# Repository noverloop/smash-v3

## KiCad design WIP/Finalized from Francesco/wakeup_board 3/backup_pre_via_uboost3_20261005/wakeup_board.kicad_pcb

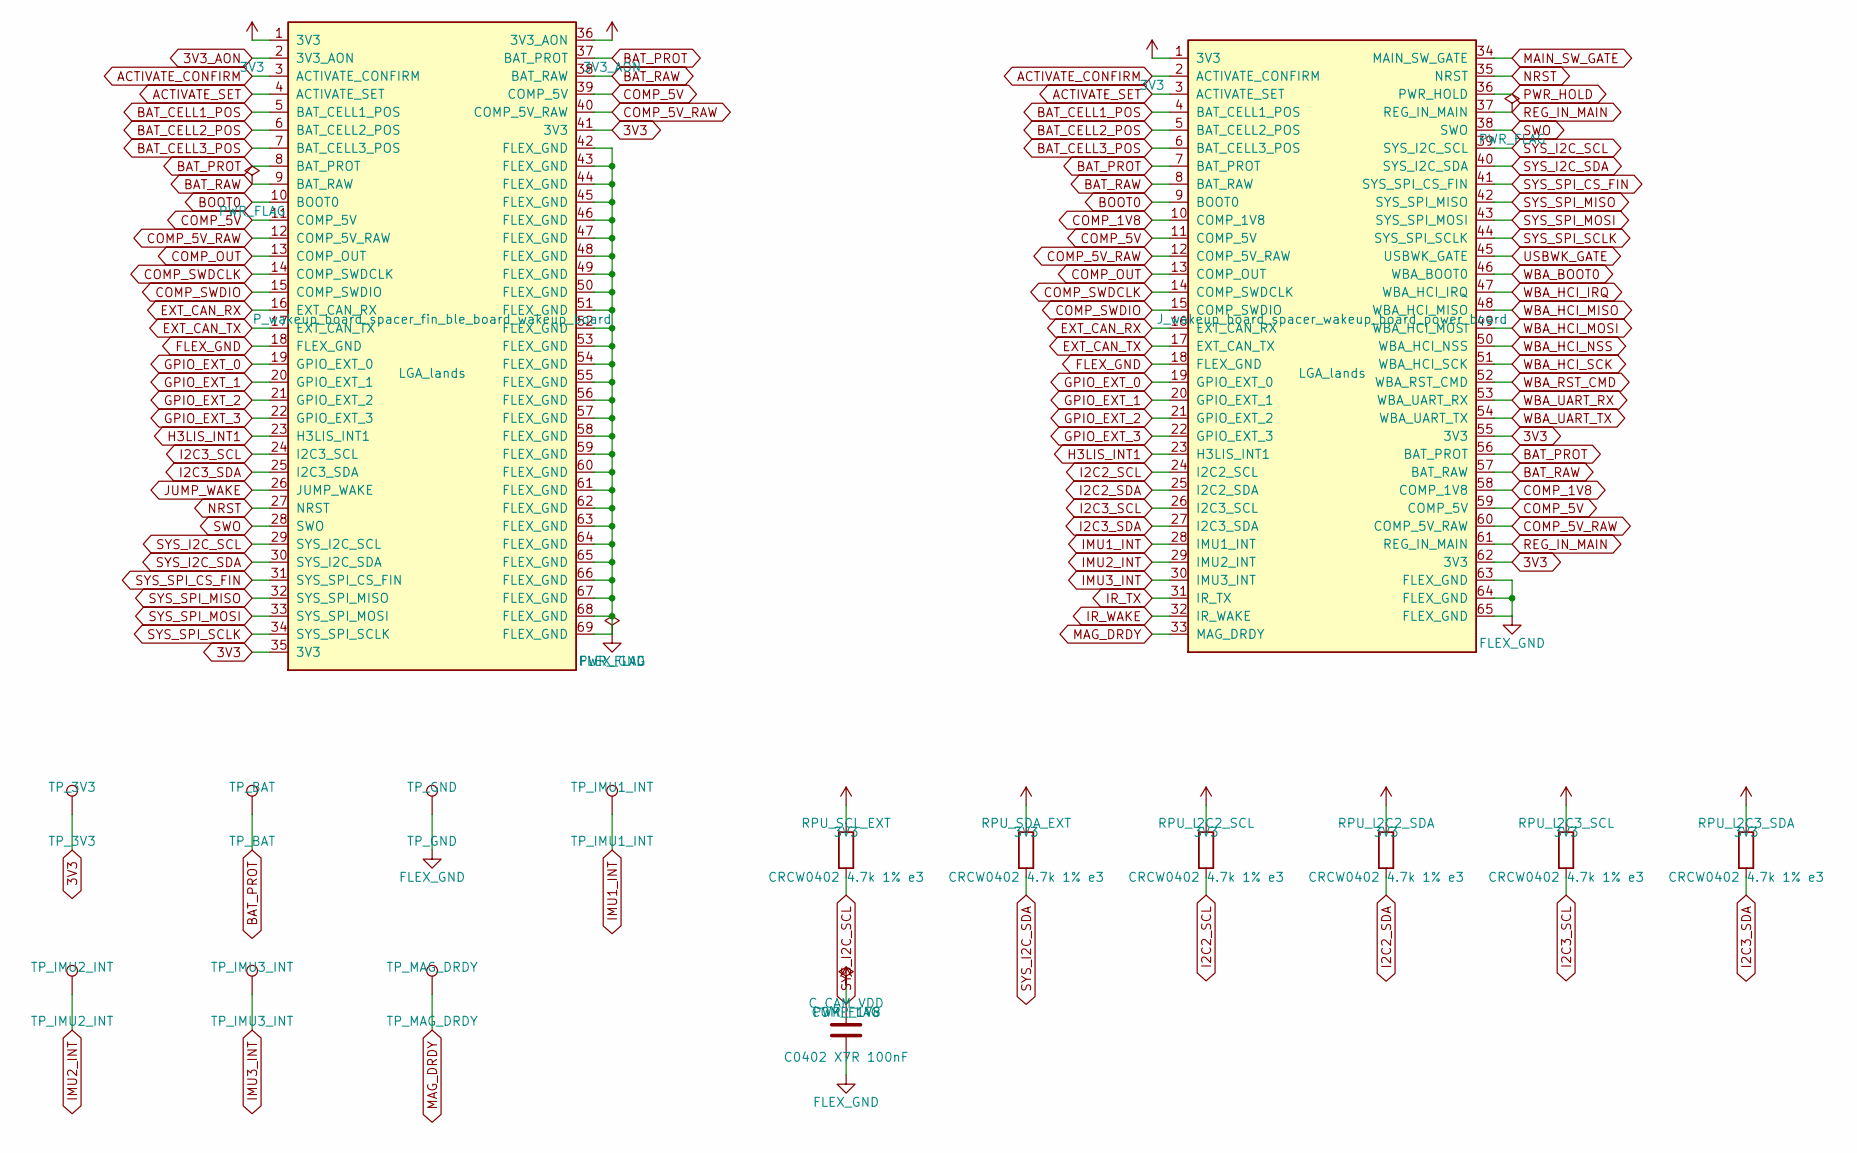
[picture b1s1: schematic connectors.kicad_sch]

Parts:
C_CAM_VDD: C0402 X7R 100nF; Capacitor_SMD_C_0402_1005Metric
J_wakeup_board_spacer_wakeup_board_power_board: LGA_lands; J_wakeup_board_spacer_wakeup_board_power_board
P_wakeup_board_spacer_fin_ble_board_wakeup_board: LGA_lands; P_wakeup_board_spacer_fin_ble_board_wakeup_board
RPU_I2C2_SCL, RPU_I2C2_SDA, RPU_I2C3_SCL, RPU_I2C3_SDA: CRCW0402 4.7k 1% e3; Resistor_SMD_R_0402_1005Metric
RPU_SCL_EXT: CRCW0402 4.7k 1% e3; Resistor_SMD_R_0402_1005Metric
RPU_SDA_EXT: CRCW0402 4.7k 1% e3; Resistor_SMD_R_0402_1005Metric
TP_3V3: TP_3V3; TestPoint_TestPoint_Pad_D1.5mm
TP_BAT: TP_BAT; TestPoint_TestPoint_Pad_D1.5mm
TP_GND: TP_GND; TestPoint_TestPoint_Pad_D1.5mm
TP_IMU1_INT: TP_IMU1_INT; TestPoint_TestPoint_Pad_D1.5mm
TP_IMU2_INT: TP_IMU2_INT; TestPoint_TestPoint_Pad_D1.5mm
TP_IMU3_INT: TP_IMU3_INT; TestPoint_TestPoint_Pad_D1.5mm
TP_MAG_DRDY: TP_MAG_DRDY; TestPoint_TestPoint_Pad_D1.5mm

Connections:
3V3: J_wakeup_board_spacer_wakeup_board_powe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.1 (3V3), J_wakeup_board_spacer_wakeup_board_powe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.55 (3V3), J_wakeup_board_spacer_wakeup_board_powe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.62 (3V3), P_wakeup_board_spacer_fin_ble_board_wak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.1 (3V3), P_wakeup_board_spacer_fin_ble_board_wak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.35 (3V3), P_wakeup_board_spacer_fin_ble_board_wak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.41 (3V3), RPU_I2C2_SCL.1, RPU_I2C2_SDA.1, RPU_I2C3_SCL.1, RPU_I2C3_SDA.1, RPU_SCL_EXT.1, RPU_SDA_EXT.1, TP_3V3.1; also elsewhere on the board
3V3_AON: P_wakeup_board_spacer_fin_ble_board_wak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.2 (3V3_AON), P_wakeup_board_spacer_fin_ble_board_wak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.36 (3V3_AON); also elsewhere on the board
ACTIVATE_CONFIRM: J_wakeup_board_spacer_wakeup_board_powe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.2 (ACTIVATE_CONFIRM), P_wakeup_board_spacer_fin_ble_board_wak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.3 (ACTIVATE_CONFIRM)
ACTIVATE_SET: J_wakeup_board_spacer_wakeup_board_powe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.3 (ACTIVATE_SET), P_wakeup_board_spacer_fin_ble_board_wak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.4 (ACTIVATE_SET)
BAT_CELL1_POS: J_wakeup_board_spacer_wakeup_board_powe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.4 (BAT_CELL1_POS), P_wakeup_board_spacer_fin_ble_board_wak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.5 (BAT_CELL1_POS)
BAT_CELL2_POS: J_wakeup_board_spacer_wakeup_board_powe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.5 (BAT_CELL2_POS), P_wakeup_board_spacer_fin_ble_board_wak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.6 (BAT_CELL2_POS)
BAT_CELL3_POS: J_wakeup_board_spacer_wakeup_board_powe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.6 (BAT_CELL3_POS), P_wakeup_board_spacer_fin_ble_board_wak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.7 (BAT_CELL3_POS)
BAT_PROT: J_wakeup_board_spacer_wakeup_board_powe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.7 (BAT_PROT), J_wakeup_board_spacer_wakeup_board_powe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.56 (BAT_PROT), P_wakeup_board_spacer_fin_ble_board_wak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.8 (BAT_PROT), P_wakeup_board_spacer_fin_ble_board_wak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.37 (BAT_PROT), TP_BAT.1; also elsewhere on the board
BAT_RAW: J_wakeup_board_spacer_wakeup_board_powe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.8 (BAT_RAW), J_wakeup_board_spacer_wakeup_board_powe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.57 (BAT_RAW), P_wakeup_board_spacer_fin_ble_board_wak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.9 (BAT_RAW), P_wakeup_board_spacer_fin_ble_board_wak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.38 (BAT_RAW); also elsewhere on the board
BOOT0: J_wakeup_board_spacer_wakeup_board_powe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.9 (BOOT0), P_wakeup_board_spacer_fin_ble_board_wak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.10 (BOOT0)
COMP_1V8: C_CAM_VDD.1, J_wakeup_board_spacer_wakeup_board_powe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.10 (COMP_1V8), J_wakeup_board_spacer_wakeup_board_powe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.58 (COMP_1V8)
COMP_5V: J_wakeup_board_spacer_wakeup_board_powe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.11 (COMP_5V), J_wakeup_board_spacer_wakeup_board_powe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.59 (COMP_5V), P_wakeup_board_spacer_fin_ble_board_wak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.11 (COMP_5V), P_wakeup_board_spacer_fin_ble_board_wak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.39 (COMP_5V)
COMP_5V_RAW: J_wakeup_board_spacer_wakeup_board_powe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.12 (COMP_5V_RAW), J_wakeup_board_spacer_wakeup_board_powe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.60 (COMP_5V_RAW), P_wakeup_board_spacer_fin_ble_board_wak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.12 (COMP_5V_RAW), P_wakeup_board_spacer_fin_ble_board_wak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.40 (COMP_5V_RAW)
COMP_OUT: J_wakeup_board_spacer_wakeup_board_powe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.13 (COMP_OUT), P_wakeup_board_spacer_fin_ble_board_wak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.13 (COMP_OUT)
COMP_SWDCLK: J_wakeup_board_spacer_wakeup_board_powe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.14 (COMP_SWDCLK), P_wakeup_board_spacer_fin_ble_board_wak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.14 (COMP_SWDCLK)
COMP_SWDIO: J_wakeup_board_spacer_wakeup_board_powe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.15 (COMP_SWDIO), P_wakeup_board_spacer_fin_ble_board_wak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.15 (COMP_SWDIO)
EXT_CAN_RX: J_wakeup_board_spacer_wakeup_board_powe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.16 (EXT_CAN_RX), P_wakeup_board_spacer_fin_ble_board_wak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.16 (EXT_CAN_RX)
EXT_CAN_TX: J_wakeup_board_spacer_wakeup_board_powe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.17 (EXT_CAN_TX), P_wakeup_board_spacer_fin_ble_board_wak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.17 (EXT_CAN_TX)
FLEX_GND: C_CAM_VDD.2, J_wakeup_board_spacer_wakeup_board_powe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.18 (FLEX_GND), J_wakeup_board_spacer_wakeup_board_powe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.63 (FLEX_GND), J_wakeup_board_spacer_wakeup_board_powe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.64 (FLEX_GND), J_wakeup_board_spacer_wakeup_board_powe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.65 (FLEX_GND), P_wakeup_board_spacer_fin_ble_board_wak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.18 (FLEX_GND), P_wakeup_board_spacer_fin_ble_board_wak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.42 (FLEX_GND), P_wakeup_board_spacer_fin_ble_board_wak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.43 (FLEX_GND), P_wakeup_board_spacer_fin_ble_board_wak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.44 (FLEX_GND), P_wakeup_board_spacer_fin_ble_board_wak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.45 (FLEX_GND), P_wakeup_board_spacer_fin_ble_board_wak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.46 (FLEX_GND), P_wakeup_board_spacer_fin_ble_board_wak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.47 (FLEX_GND), P_wakeup_board_spacer_fin_ble_board_wak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.48 (FLEX_GND), P_wakeup_board_spacer_fin_ble_board_wak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.49 (FLEX_GND), P_wakeup_board_spacer_fin_ble_board_wak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.50 (FLEX_GND), P_wakeup_board_spacer_fin_ble_board_wak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.51 (FLEX_GND), P_wakeup_board_spacer_fin_ble_board_wak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.52 (FLEX_GND), P_wakeup_board_spacer_fin_ble_board_wak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.53 (FLEX_GND), P_wakeup_board_spacer_fin_ble_board_wak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.54 (FLEX_GND), P_wakeup_board_spacer_fin_ble_board_wak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.55 (FLEX_GND), P_wakeup_board_spacer_fin_ble_board_wak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.56 (FLEX_GND), P_wakeup_board_spacer_fin_ble_board_wak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.57 (FLEX_GND), P_wakeup_board_spacer_fin_ble_board_wak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.58 (FLEX_GND), P_wakeup_board_spacer_fin_ble_board_wak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.59 (FLEX_GND), P_wakeup_board_spacer_fin_ble_board_wak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.60 (FLEX_GND), P_wakeup_board_spacer_fin_ble_board_wak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.61 (FLEX_GND), P_wakeup_board_spacer_fin_ble_board_wak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.62 (FLEX_GND), P_wakeup_board_spacer_fin_ble_board_wak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.63 (FLEX_GND), P_wakeup_board_spacer_fin_ble_board_wak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.64 (FLEX_GND), P_wakeup_board_spacer_fin_ble_board_wak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.65 (FLEX_GND), P_wakeup_board_spacer_fin_ble_board_wak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.66 (FLEX_GND), P_wakeup_board_spacer_fin_ble_board_wak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.67 (FLEX_GND), P_wakeup_board_spacer_fin_ble_board_wak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.68 (FLEX_GND), P_wakeup_board_spacer_fin_ble_board_wak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.69 (FLEX_GND), TP_GND.1; also elsewhere on the board
GPIO_EXT_0: J_wakeup_board_spacer_wakeup_board_powe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.19 (GPIO_EXT_0), P_wakeup_board_spacer_fin_ble_board_wak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.19 (GPIO_EXT_0)
GPIO_EXT_1: J_wakeup_board_spacer_wakeup_board_powe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.20 (GPIO_EXT_1), P_wakeup_board_spacer_fin_ble_board_wak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.20 (GPIO_EXT_1)
GPIO_EXT_2: J_wakeup_board_spacer_wakeup_board_powe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.21 (GPIO_EXT_2), P_wakeup_board_spacer_fin_ble_board_wak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.21 (GPIO_EXT_2)
GPIO_EXT_3: J_wakeup_board_spacer_wakeup_board_powe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.22 (GPIO_EXT_3), P_wakeup_board_spacer_fin_ble_board_wak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.22 (GPIO_EXT_3)
H3LIS_INT1: J_wakeup_board_spacer_wakeup_board_powe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.23 (H3LIS_INT1), P_wakeup_board_spacer_fin_ble_board_wak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.23 (H3LIS_INT1)
I2C2_SCL: J_wakeup_board_spacer_wakeup_board_powe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.24 (I2C2_SCL), RPU_I2C2_SCL.2; also elsewhere on the board
I2C2_SDA: J_wakeup_board_spacer_wakeup_board_powe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.25 (I2C2_SDA), RPU_I2C2_SDA.2; also elsewhere on the board
I2C3_SCL: J_wakeup_board_spacer_wakeup_board_powe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.26 (I2C3_SCL), P_wakeup_board_spacer_fin_ble_board_wak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.24 (I2C3_SCL), RPU_I2C3_SCL.2; also elsewhere on the board
I2C3_SDA: J_wakeup_board_spacer_wakeup_board_powe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.27 (I2C3_SDA), P_wakeup_board_spacer_fin_ble_board_wak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.25 (I2C3_SDA), RPU_I2C3_SDA.2; also elsewhere on the board
IMU1_INT: J_wakeup_board_spacer_wakeup_board_powe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.28 (IMU1_INT), TP_IMU1_INT.1; also elsewhere on the board
IMU2_INT: J_wakeup_board_spacer_wakeup_board_powe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.29 (IMU2_INT), TP_IMU2_INT.1; also elsewhere on the board
IMU3_INT: J_wakeup_board_spacer_wakeup_board_powe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.30 (IMU3_INT), TP_IMU3_INT.1; also elsewhere on the board
IR_TX: J_wakeup_board_spacer_wakeup_board_powe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.31 (IR_TX); also elsewhere on the board
IR_WAKE: J_wakeup_board_spacer_wakeup_board_powe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.32 (IR_WAKE); also elsewhere on the board
MAG_DRDY: J_wakeup_board_spacer_wakeup_board_powe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.33 (MAG_DRDY), TP_MAG_DRDY.1; also elsewhere on the board
MAIN_SW_GATE: J_wakeup_board_spacer_wakeup_board_powe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.34 (MAIN_SW_GATE); also elsewhere on the board
NRST: J_wakeup_board_spacer_wakeup_board_powe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.35 (NRST), P_wakeup_board_spacer_fin_ble_board_wak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.27 (NRST)
PWR_HOLD: J_wakeup_board_spacer_wakeup_board_powe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.36 (PWR_HOLD); also elsewhere on the board
REG_IN_MAIN: J_wakeup_board_spacer_wakeup_board_powe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.37 (REG_IN_MAIN), J_wakeup_board_spacer_wakeup_board_powe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.61 (REG_IN_MAIN); also elsewhere on the board
SWO: J_wakeup_board_spacer_wakeup_board_powe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.38 (SWO), P_wakeup_board_spacer_fin_ble_board_wak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.28 (SWO)
SYS_I2C_SCL: J_wakeup_board_spacer_wakeup_board_powe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.39 (SYS_I2C_SCL), P_wakeup_board_spacer_fin_ble_board_wak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.29 (SYS_I2C_SCL), RPU_SCL_EXT.2
SYS_I2C_SDA: J_wakeup_board_spacer_wakeup_board_powe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.40 (SYS_I2C_SDA), P_wakeup_board_spacer_fin_ble_board_wak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.30 (SYS_I2C_SDA), RPU_SDA_EXT.2
SYS_SPI_CS_FIN: J_wakeup_board_spacer_wakeup_board_powe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.41 (SYS_SPI_CS_FIN), P_wakeup_board_spacer_fin_ble_board_wak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.31 (SYS_SPI_CS_FIN)
SYS_SPI_MISO: J_wakeup_board_spacer_wakeup_board_powe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.42 (SYS_SPI_MISO), P_wakeup_board_spacer_fin_ble_board_wak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.32 (SYS_SPI_MISO)
SYS_SPI_MOSI: J_wakeup_board_spacer_wakeup_board_powe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.43 (SYS_SPI_MOSI), P_wakeup_board_spacer_fin_ble_board_wak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.33 (SYS_SPI_MOSI)
SYS_SPI_SCLK: J_wakeup_board_spacer_wakeup_board_powe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.44 (SYS_SPI_SCLK), P_wakeup_board_spacer_fin_ble_board_wak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.34 (SYS_SPI_SCLK)
USBWK_GATE: J_wakeup_board_spacer_wakeup_board_powe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.45 (USBWK_GATE); also elsewhere on the board
WBA_BOOT0: J_wakeup_board_spacer_wakeup_board_powe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.46 (WBA_BOOT0); also elsewhere on the board
WBA_HCI_IRQ: J_wakeup_board_spacer_wakeup_board_powe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.47 (WBA_HCI_IRQ); also elsewhere on the board
WBA_HCI_MISO: J_wakeup_board_spacer_wakeup_board_powe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.48 (WBA_HCI_MISO); also elsewhere on the board
WBA_HCI_MOSI: J_wakeup_board_spacer_wakeup_board_powe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.49 (WBA_HCI_MOSI); also elsewhere on the board
WBA_HCI_NSS: J_wakeup_board_spacer_wakeup_board_powe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.50 (WBA_HCI_NSS); also elsewhere on the board
WBA_HCI_SCK: J_wakeup_board_spacer_wakeup_board_powe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.51 (WBA_HCI_SCK); also elsewhere on the board
WBA_RST_CMD: J_wakeup_board_spacer_wakeup_board_powe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.52 (WBA_RST_CMD); also elsewhere on the board
WBA_UART_RX: J_wakeup_board_spacer_wakeup_board_powe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.53 (WBA_UART_RX); also elsewhere on the board
WBA_UART_TX: J_wakeup_board_spacer_wakeup_board_powe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.54 (WBA_UART_TX); also elsewhere on the board

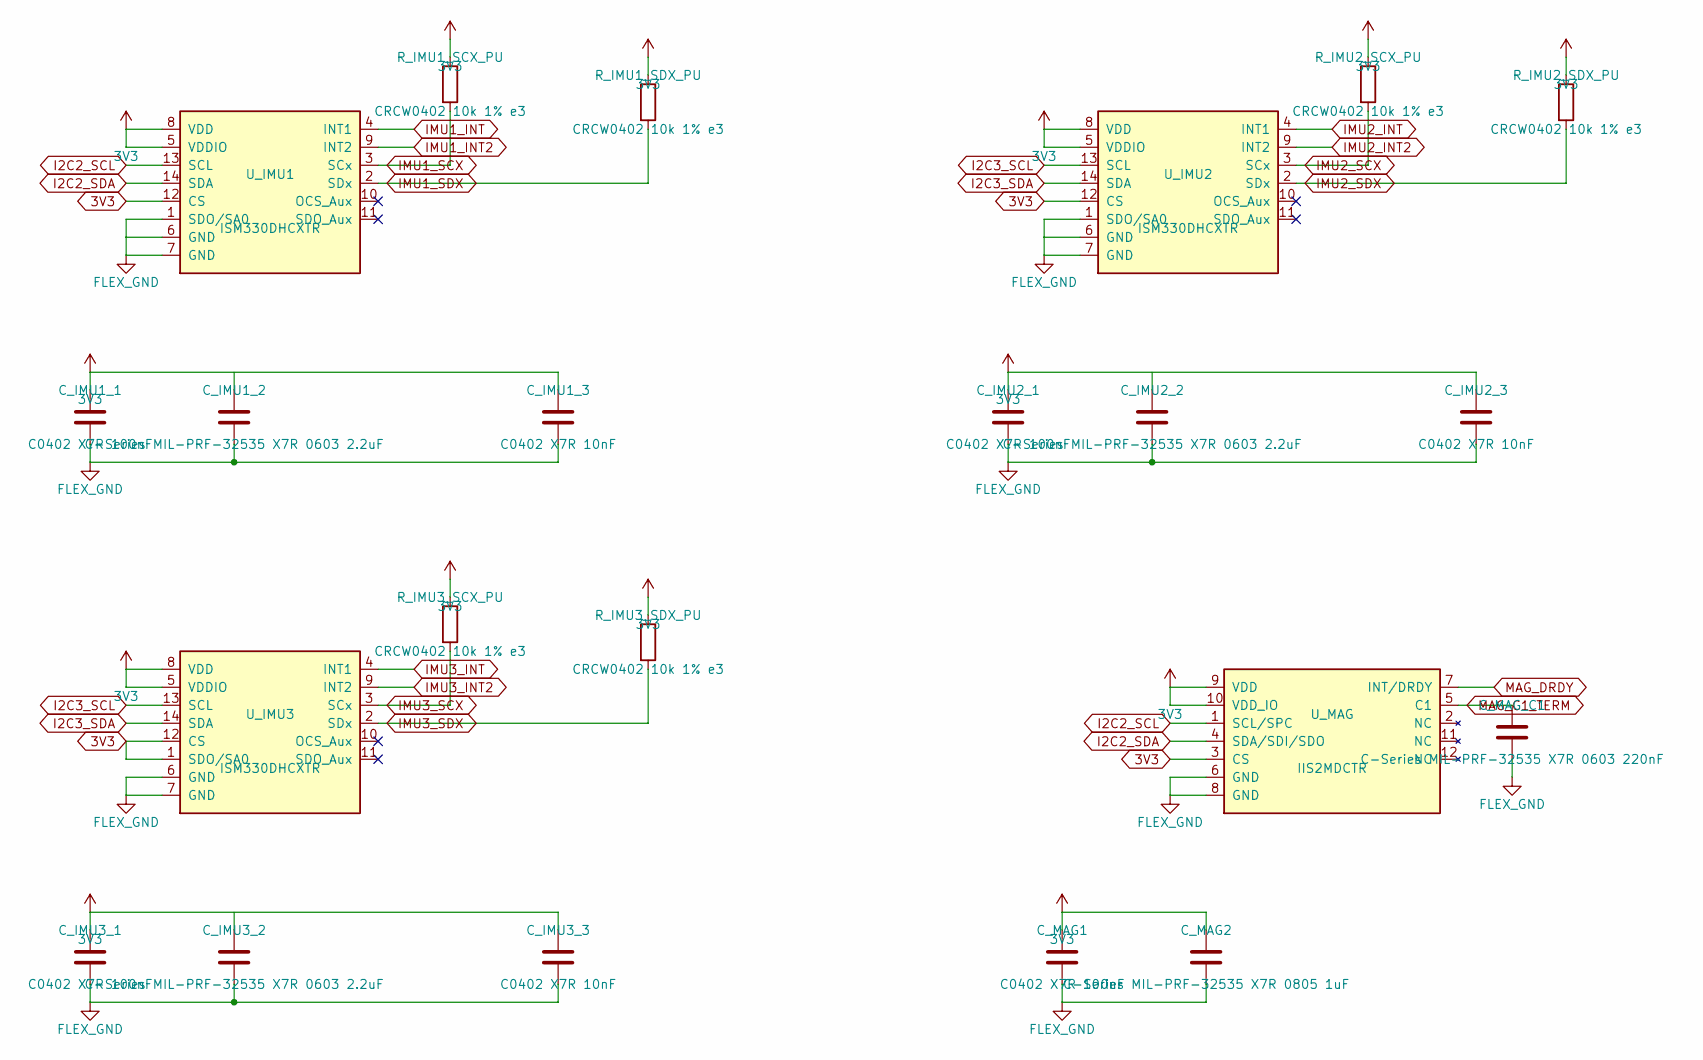
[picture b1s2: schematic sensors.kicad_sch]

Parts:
C_IMU1_1, C_IMU2_1, C_IMU3_1: C0402 X7R 100nF; Capacitor_SMD_C_0402_1005Metric
C_IMU1_2, C_IMU2_2, C_IMU3_2: C-Series MIL-PRF-32535 X7R 0603 2.2uF; Capacitor_SMD_C_0603_1608Metric
C_IMU1_3, C_IMU2_3, C_IMU3_3: C0402 X7R 10nF; Capacitor_SMD_C_0402_1005Metric
C_MAG1: C0402 X7R 100nF; Capacitor_SMD_C_0402_1005Metric
C_MAG2: C-Series MIL-PRF-32535 X7R 0805 1uF; Capacitor_SMD_C_0805_2012Metric
C_MAG_C1: C-Series MIL-PRF-32535 X7R 0603 220nF; Capacitor_SMD_C_0603_1608Metric
R_IMU1_SCX_PU, R_IMU1_SDX_PU, R_IMU2_SCX_PU, R_IMU2_SDX_PU, R_IMU3_SCX_PU, R_IMU3_SDX_PU: CRCW0402 10k 1% e3; Resistor_SMD_R_0402_1005Metric
U_IMU1, U_IMU2, U_IMU3: ISM330DHCXTR; LSM6DS3USTR (LGA-14)
U_MAG: IIS2MDCTR

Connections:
3V3: C_IMU1_1.1, C_IMU1_2.1, C_IMU1_3.1, C_IMU2_1.1, C_IMU2_2.1, C_IMU2_3.1, C_IMU3_1.1, C_IMU3_2.1, C_IMU3_3.1, C_MAG1.1, C_MAG2.1, R_IMU1_SCX_PU.1, R_IMU1_SDX_PU.1, R_IMU2_SCX_PU.1, R_IMU2_SDX_PU.1, R_IMU3_SCX_PU.1, R_IMU3_SDX_PU.1, U_IMU1.5 (VDDIO), U_IMU1.8 (VDD), U_IMU1.12 (CS), U_IMU2.5 (VDDIO), U_IMU2.8 (VDD), U_IMU2.12 (CS), U_IMU3.1 (SDO/SA0), U_IMU3.5 (VDDIO), U_IMU3.8 (VDD), U_IMU3.12 (CS), U_MAG.3 (CS), U_MAG.9 (VDD), U_MAG.10 (VDD_IO); also elsewhere on the board
FLEX_GND: C_IMU1_1.2, C_IMU1_2.2, C_IMU1_3.2, C_IMU2_1.2, C_IMU2_2.2, C_IMU2_3.2, C_IMU3_1.2, C_IMU3_2.2, C_IMU3_3.2, C_MAG1.2, C_MAG2.2, C_MAG_C1.2, U_IMU1.1 (SDO/SA0), U_IMU1.6 (GND), U_IMU1.7 (GND), U_IMU2.1 (SDO/SA0), U_IMU2.6 (GND), U_IMU2.7 (GND), U_IMU3.6 (GND), U_IMU3.7 (GND), U_MAG.6 (GND), U_MAG.8 (GND); also elsewhere on the board
I2C2_SCL: U_IMU1.13 (SCL), U_MAG.1 (SCL/SPC); also elsewhere on the board
I2C2_SDA: U_IMU1.14 (SDA), U_MAG.4 (SDA/SDI/SDO); also elsewhere on the board
I2C3_SCL: U_IMU2.13 (SCL), U_IMU3.13 (SCL); also elsewhere on the board
I2C3_SDA: U_IMU2.14 (SDA), U_IMU3.14 (SDA); also elsewhere on the board
IMU1_INT: U_IMU1.4 (INT1); also elsewhere on the board
IMU1_INT2: U_IMU1.9 (INT2)
IMU1_SCX: R_IMU1_SCX_PU.2, U_IMU1.3 (SCx)
IMU1_SDX: R_IMU1_SDX_PU.2, U_IMU1.2 (SDx)
IMU2_INT: U_IMU2.4 (INT1); also elsewhere on the board
IMU2_INT2: U_IMU2.9 (INT2)
IMU2_SCX: R_IMU2_SCX_PU.2, U_IMU2.3 (SCx)
IMU2_SDX: R_IMU2_SDX_PU.2, U_IMU2.2 (SDx)
IMU3_INT: U_IMU3.4 (INT1); also elsewhere on the board
IMU3_INT2: U_IMU3.9 (INT2)
IMU3_SCX: R_IMU3_SCX_PU.2, U_IMU3.3 (SCx)
IMU3_SDX: R_IMU3_SDX_PU.2, U_IMU3.2 (SDx)
MAG_C1_TERM: C_MAG_C1.1, U_MAG.5 (C1)
MAG_DRDY: U_MAG.7 (INT/DRDY); also elsewhere on the board

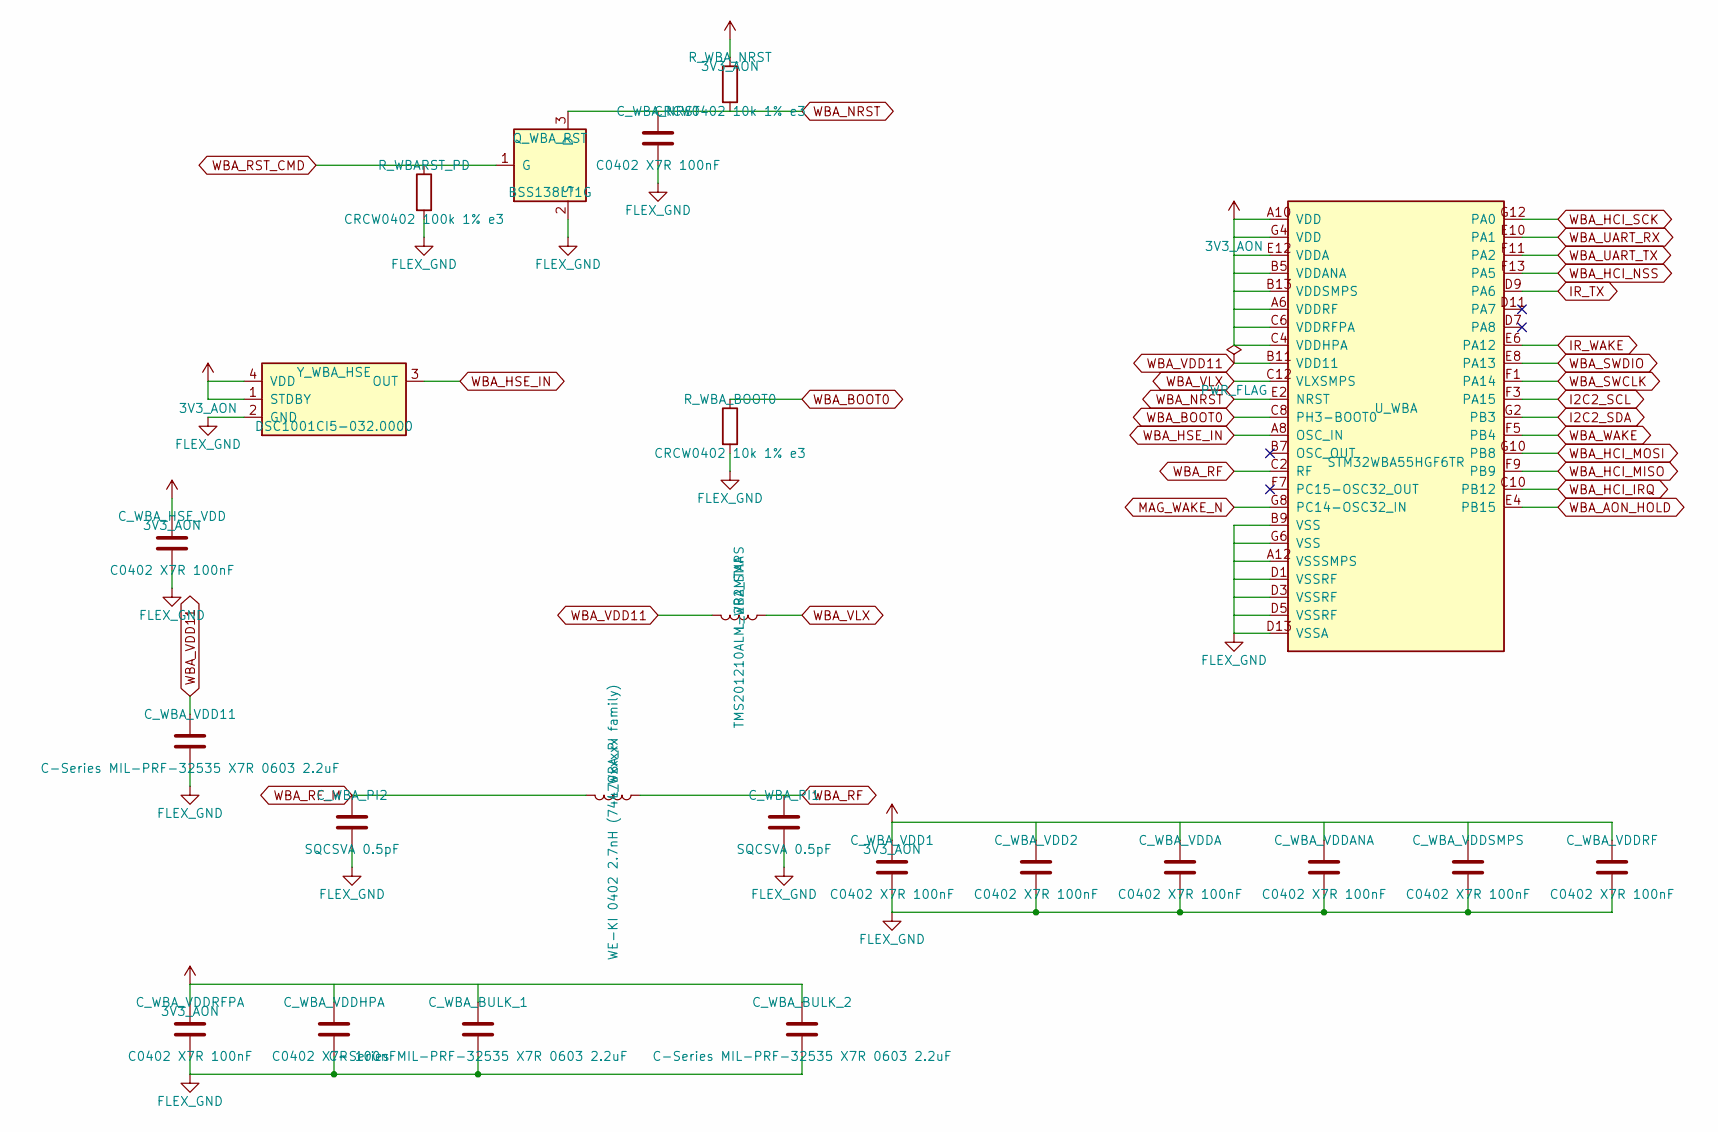
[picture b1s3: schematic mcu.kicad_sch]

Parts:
C_WBA_BULK_1, C_WBA_BULK_2: C-Series MIL-PRF-32535 X7R 0603 2.2uF; Capacitor_SMD_C_0603_1608Metric
C_WBA_HSE_VDD: C0402 X7R 100nF; Capacitor_SMD_C_0402_1005Metric
C_WBA_NRST: C0402 X7R 100nF; Capacitor_SMD_C_0402_1005Metric
C_WBA_PI1: SQCSVA 0.5pF; Capacitor_SMD_C_0402_1005Metric
C_WBA_PI2: SQCSVA 0.5pF; Capacitor_SMD_C_0603_1608Metric
C_WBA_VDD1, C_WBA_VDD2: C0402 X7R 100nF; Capacitor_SMD_C_0402_1005Metric
C_WBA_VDD11: C-Series MIL-PRF-32535 X7R 0603 2.2uF; Capacitor_SMD_C_0402_1005Metric
C_WBA_VDDA: C0402 X7R 100nF; Capacitor_SMD_C_0402_1005Metric
C_WBA_VDDANA: C0402 X7R 100nF; Capacitor_SMD_C_0402_1005Metric
C_WBA_VDDHPA: C0402 X7R 100nF; Capacitor_SMD_C_0402_1005Metric
C_WBA_VDDRF: C0402 X7R 100nF; Capacitor_SMD_C_0402_1005Metric
C_WBA_VDDRFPA: C0402 X7R 100nF; Capacitor_SMD_C_0402_1005Metric
C_WBA_VDDSMPS: C0402 X7R 100nF; Capacitor_SMD_C_0402_1005Metric
L_WBA_PI: WE-KI 0402 2.7nH (74479xxxxx family); Inductor_SMD_L_0402_1005Metric
L_WBA_SMPS: TMS201210ALM-2R2MTAA; Inductor_SMD_L_2012_2.0x1.25mm
Q_WBA_RST: BSS138LT1G; SOT96P237X111-3N
R_WBARST_PD: CRCW0402 100k 1% e3; Resistor_SMD_R_0402_1005Metric
R_WBA_BOOT0: CRCW0402 10k 1% e3; Resistor_SMD_R_0402_1005Metric
R_WBA_NRST: CRCW0402 10k 1% e3; Resistor_SMD_R_0402_1005Metric
U_WBA: STM32WBA55HGF6TR; BGA41C35P13X7_298X276X50
Y_WBA_HSE: DSC1001CI5-032.0000; DSC1001CI50080000

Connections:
3V3_AON: C_WBA_BULK_1.1, C_WBA_BULK_2.1, C_WBA_HSE_VDD.1, C_WBA_VDD1.1, C_WBA_VDD2.1, C_WBA_VDDA.1, C_WBA_VDDANA.1, C_WBA_VDDHPA.1, C_WBA_VDDRF.1, C_WBA_VDDRFPA.1, C_WBA_VDDSMPS.1, R_WBA_NRST.1, U_WBA.A6 (VDDRF), U_WBA.A10 (VDD), U_WBA.B5 (VDDANA), U_WBA.B13 (VDDSMPS), U_WBA.C4 (VDDHPA), U_WBA.C6 (VDDRFPA), U_WBA.E12 (VDDA), U_WBA.G4 (VDD), Y_WBA_HSE.1 (STDBY), Y_WBA_HSE.4 (VDD); also elsewhere on the board
FLEX_GND: C_WBA_BULK_1.2, C_WBA_BULK_2.2, C_WBA_HSE_VDD.2, C_WBA_NRST.2, C_WBA_PI1.2, C_WBA_PI2.2, C_WBA_VDD1.2, C_WBA_VDD2.2, C_WBA_VDD11.2, C_WBA_VDDA.2, C_WBA_VDDANA.2, C_WBA_VDDHPA.2, C_WBA_VDDRF.2, C_WBA_VDDRFPA.2, C_WBA_VDDSMPS.2, Q_WBA_RST.2 (S), R_WBARST_PD.2, R_WBA_BOOT0.2, U_WBA.A12 (VSSSMPS), U_WBA.B9 (VSS), U_WBA.D1 (VSSRF), U_WBA.D3 (VSSRF), U_WBA.D5 (VSSRF), U_WBA.D13 (VSSA), U_WBA.G6 (VSS), Y_WBA_HSE.2 (GND); also elsewhere on the board
I2C2_SCL: U_WBA.F3 (PA15); also elsewhere on the board
I2C2_SDA: U_WBA.G2 (PB3); also elsewhere on the board
IR_TX: U_WBA.D9 (PA6); also elsewhere on the board
IR_WAKE: U_WBA.E6 (PA12); also elsewhere on the board
MAG_WAKE_N: U_WBA.G8 (PC14-OSC32_IN); also elsewhere on the board
WBA_AON_HOLD: U_WBA.E4 (PB15); also elsewhere on the board
WBA_BOOT0: R_WBA_BOOT0.1, U_WBA.C8 (PH3-BOOT0); also elsewhere on the board
WBA_HCI_IRQ: U_WBA.C10 (PB12); also elsewhere on the board
WBA_HCI_MISO: U_WBA.F9 (PB9); also elsewhere on the board
WBA_HCI_MOSI: U_WBA.G10 (PB8); also elsewhere on the board
WBA_HCI_NSS: U_WBA.F13 (PA5); also elsewhere on the board
WBA_HCI_SCK: U_WBA.G12 (PA0); also elsewhere on the board
WBA_HSE_IN: U_WBA.A8 (OSC_IN), Y_WBA_HSE.3 (OUT)
WBA_NRST: C_WBA_NRST.1, Q_WBA_RST.3 (D), R_WBA_NRST.2, U_WBA.E2 (NRST)
WBA_RF: C_WBA_PI1.1, L_WBA_PI.1, U_WBA.C2 (RF)
WBA_RF_M: C_WBA_PI2.1, L_WBA_PI.2
WBA_RST_CMD: Q_WBA_RST.1 (G), R_WBARST_PD.1; also elsewhere on the board
WBA_SWCLK: U_WBA.F1 (PA14)
WBA_SWDIO: U_WBA.E8 (PA13)
WBA_UART_RX: U_WBA.E10 (PA1); also elsewhere on the board
WBA_UART_TX: U_WBA.F11 (PA2); also elsewhere on the board
WBA_VDD11: C_WBA_VDD11.1, L_WBA_SMPS.2, U_WBA.B11 (VDD11)
WBA_VLX: L_WBA_SMPS.1, U_WBA.C12 (VLXSMPS)
WBA_WAKE: U_WBA.F5 (PB4); also elsewhere on the board

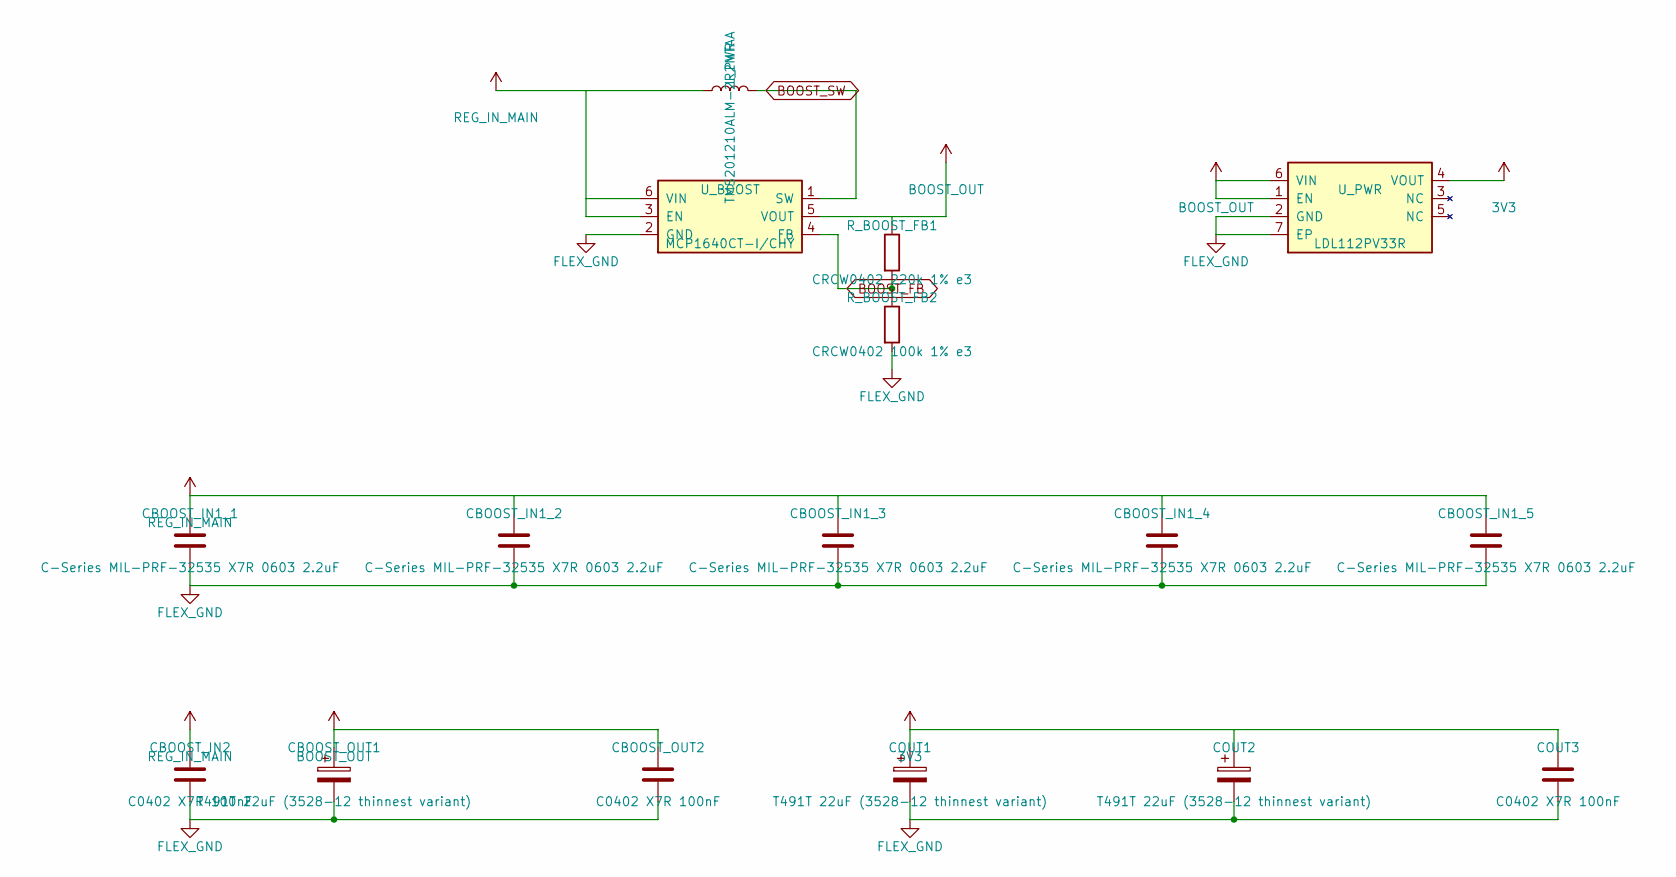
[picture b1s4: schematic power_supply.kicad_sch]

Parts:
CBOOST_IN1_1, CBOOST_IN1_2, CBOOST_IN1_3, CBOOST_IN1_4, CBOOST_IN1_5: C-Series MIL-PRF-32535 X7R 0603 2.2uF; Capacitor_SMD_C_0603_1608Metric
CBOOST_IN2: C0402 X7R 100nF; Capacitor_SMD_C_0402_1005Metric
CBOOST_OUT1: T491T 22uF (3528-12 thinnest variant); Capacitor_Tantalum_SMD_CP_EIA-3528-12_Kemet-T
CBOOST_OUT2: C0402 X7R 100nF; Capacitor_SMD_C_0402_1005Metric
COUT1, COUT2: T491T 22uF (3528-12 thinnest variant); Capacitor_Tantalum_SMD_CP_EIA-3528-12_Kemet-T
COUT3: C0402 X7R 100nF; Capacitor_SMD_C_0402_1005Metric
L_PWR: TMS201210ALM-2R2MTAA; Inductor_SMD_L_2012_2.0x1.25mm
R_BOOST_FB1: CRCW0402 220k 1% e3; Resistor_SMD_R_0402_1005Metric
R_BOOST_FB2: CRCW0402 100k 1% e3; Resistor_SMD_R_0402_1005Metric
U_BOOST: MCP1640CT-I/CHY; SOT95P270X145-6N
U_PWR: LDL112PV33R; SON95P300X300X100-7N-D

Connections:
3V3: COUT1.1, COUT2.1, COUT3.1, U_PWR.4 (VOUT); also elsewhere on the board
BOOST_FB: R_BOOST_FB1.2, R_BOOST_FB2.1, U_BOOST.4 (FB)
BOOST_OUT: CBOOST_OUT1.1, CBOOST_OUT2.1, R_BOOST_FB1.1, U_BOOST.5 (VOUT), U_PWR.1 (EN), U_PWR.6 (VIN)
BOOST_SW: L_PWR.2, U_BOOST.1 (SW)
FLEX_GND: CBOOST_IN1_1.2, CBOOST_IN1_2.2, CBOOST_IN1_3.2, CBOOST_IN1_4.2, CBOOST_IN1_5.2, CBOOST_IN2.2, CBOOST_OUT1.2, CBOOST_OUT2.2, COUT1.2, COUT2.2, COUT3.2, R_BOOST_FB2.2, U_BOOST.2 (GND), U_PWR.2 (GND), U_PWR.7 (EP); also elsewhere on the board
REG_IN_MAIN: CBOOST_IN1_1.1, CBOOST_IN1_2.1, CBOOST_IN1_3.1, CBOOST_IN1_4.1, CBOOST_IN1_5.1, CBOOST_IN2.1, L_PWR.1, U_BOOST.3 (EN), U_BOOST.6 (VIN); also elsewhere on the board

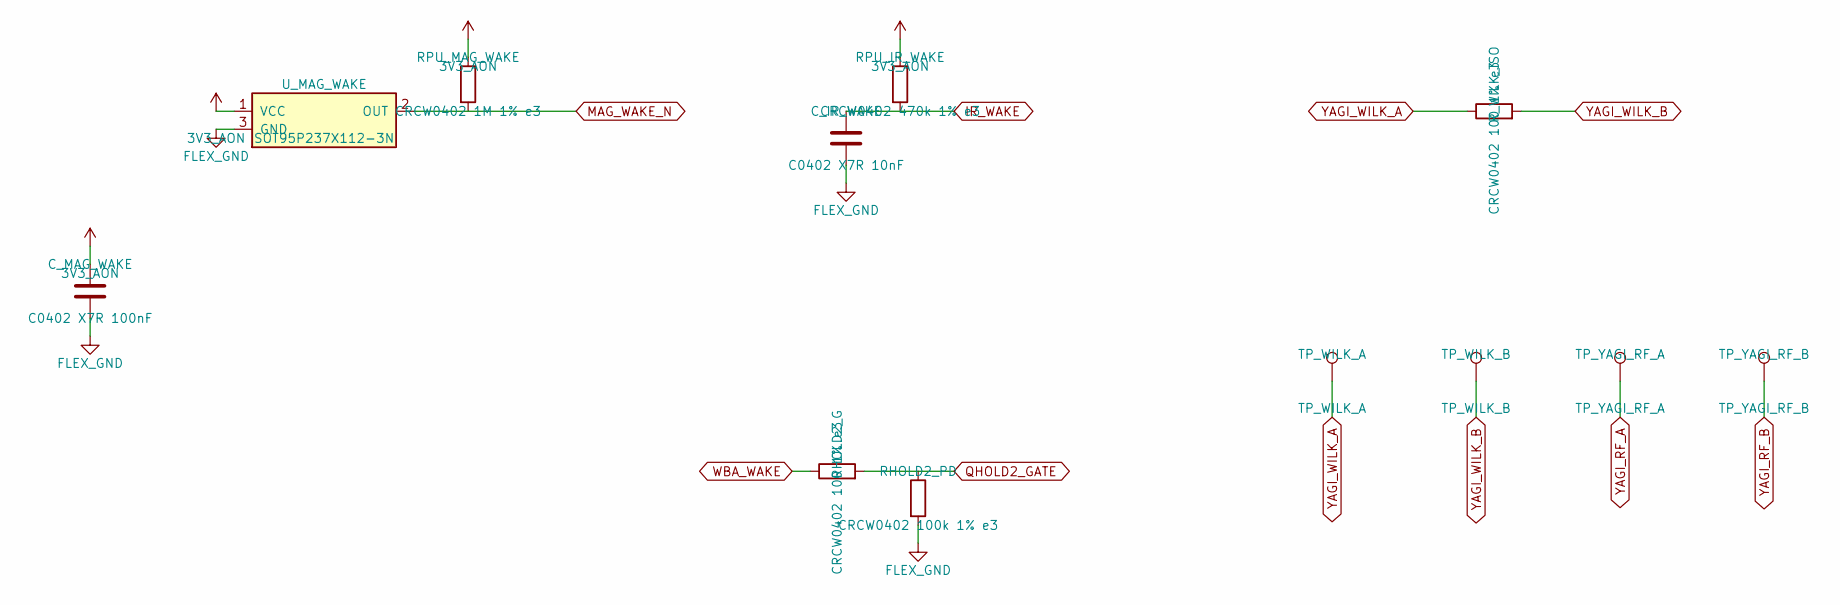
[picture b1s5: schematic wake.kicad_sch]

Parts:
C_IR_WAKE: C0402 X7R 10nF; Capacitor_SMD_C_0402_1005Metric
C_MAG_WAKE: C0402 X7R 100nF; Capacitor_SMD_C_0402_1005Metric
RHOLD2_G: CRCW0402 100 1% e3; Resistor_SMD_R_0402_1005Metric
RHOLD2_PD: CRCW0402 100k 1% e3; Resistor_SMD_R_0402_1005Metric
RPU_IR_WAKE: CRCW0402 470k 1% e3; Resistor_SMD_R_0402_1005Metric
RPU_MAG_WAKE: CRCW0402 1M 1% e3; Resistor_SMD_R_0402_1005Metric
R_WILK_ISO: CRCW0402 100 1% e3; Resistor_SMD_R_0402_1005Metric
TP_WILK_A: TP_WILK_A; TestPoint_TestPoint_Pad_D1.5mm
TP_WILK_B: TP_WILK_B; TestPoint_TestPoint_Pad_D1.5mm
TP_YAGI_RF_A: TP_YAGI_RF_A; TestPoint_TestPoint_Pad_D1.5mm
TP_YAGI_RF_B: TP_YAGI_RF_B; TestPoint_TestPoint_Pad_D1.5mm
U_MAG_WAKE: SOT95P237X112-3N

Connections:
3V3_AON: C_MAG_WAKE.1, RPU_IR_WAKE.1, RPU_MAG_WAKE.1, U_MAG_WAKE.1 (VCC); also elsewhere on the board
FLEX_GND: C_IR_WAKE.2, C_MAG_WAKE.2, RHOLD2_PD.2, U_MAG_WAKE.3 (GND); also elsewhere on the board
IR_WAKE: C_IR_WAKE.1, RPU_IR_WAKE.2; also elsewhere on the board
MAG_WAKE_N: RPU_MAG_WAKE.2, U_MAG_WAKE.2 (OUT); also elsewhere on the board
QHOLD2_GATE: RHOLD2_G.2, RHOLD2_PD.1
WBA_WAKE: RHOLD2_G.1; also elsewhere on the board
YAGI_RF_A: TP_YAGI_RF_A.1
YAGI_RF_B: TP_YAGI_RF_B.1
YAGI_WILK_A: R_WILK_ISO.1, TP_WILK_A.1
YAGI_WILK_B: R_WILK_ISO.2, TP_WILK_B.1
